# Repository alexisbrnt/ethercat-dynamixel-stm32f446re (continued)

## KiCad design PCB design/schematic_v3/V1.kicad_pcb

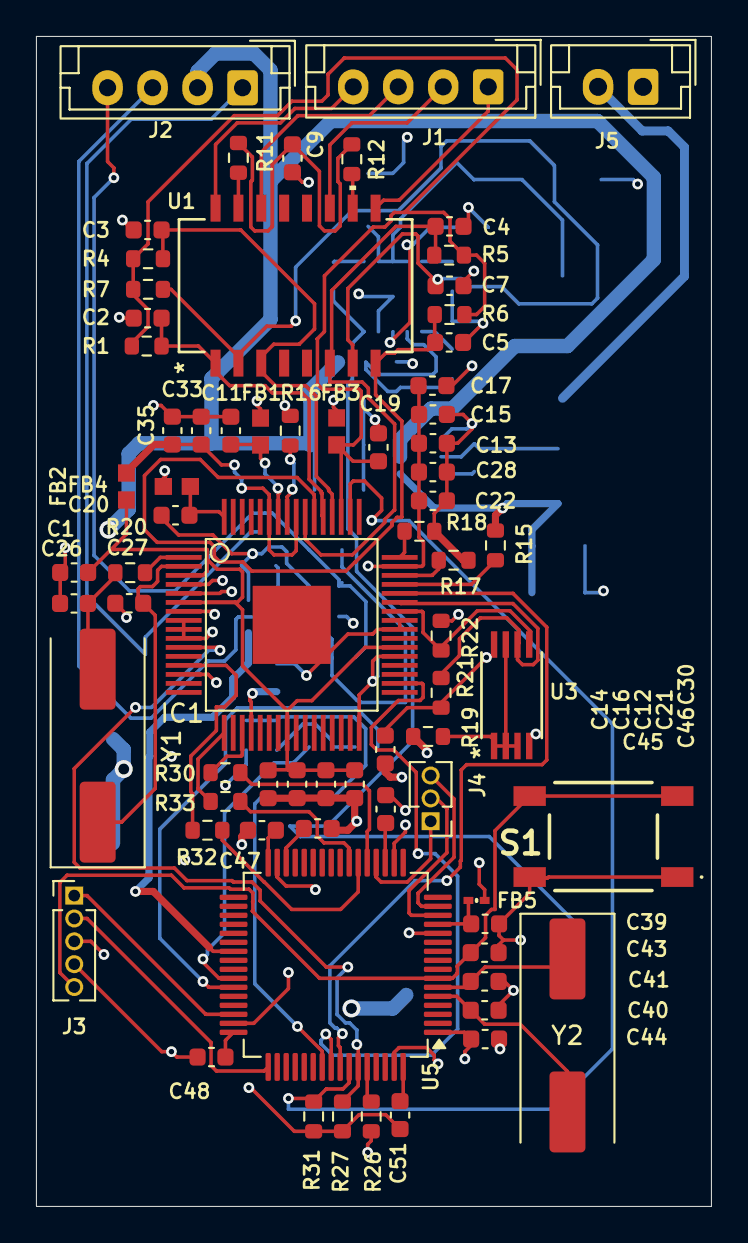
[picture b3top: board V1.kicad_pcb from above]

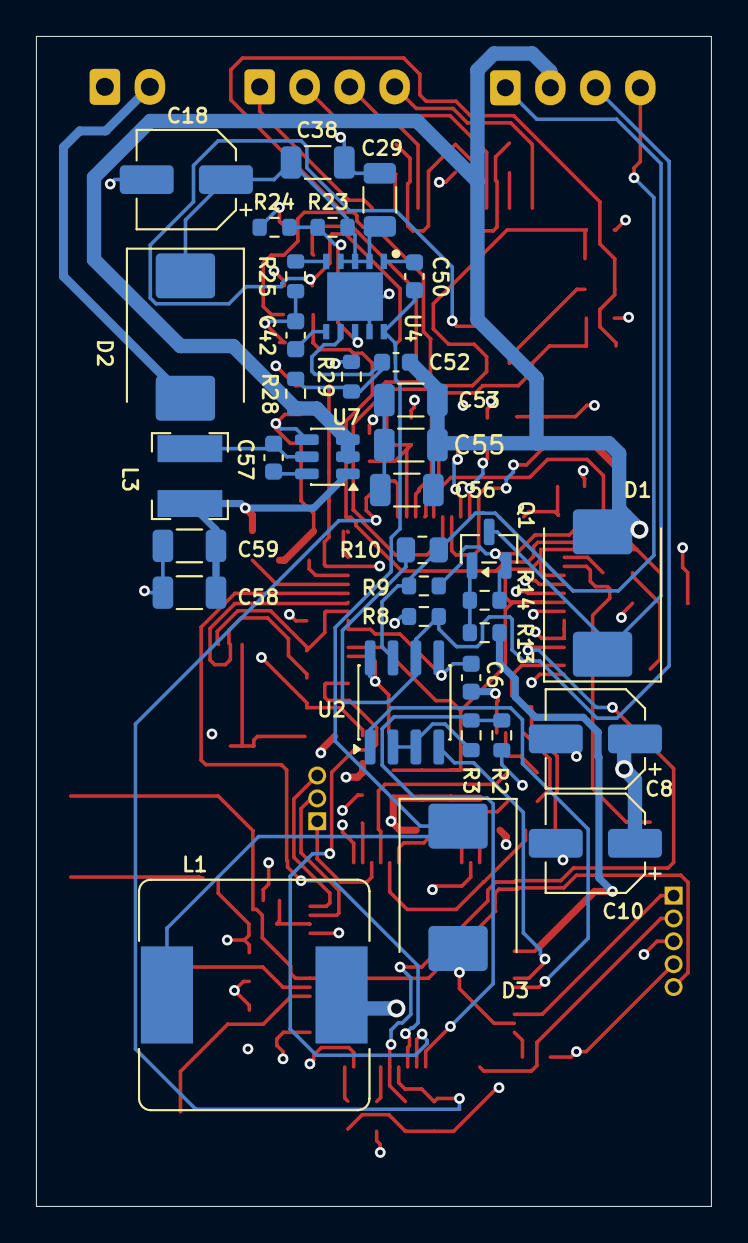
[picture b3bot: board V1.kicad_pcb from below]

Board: 4 copper layers, 37.5 x 65.0 mm, 108 parts (36 on the bottom side), 74 nets.

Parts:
C1, C6, C11, C13, C15, C16, C17, C21, C22, C28, C30, C33, C35: 0.1u; C_0603_1608Metric
C2, C3, C4, C5: 10p; C_0603_1608Metric
C7: 0.022u; C_0603_1608Metric
C8, C10, C18: 47u; CP_Elec_5x5.4
C9: 1n; C_0603_1608Metric
C12, C19, C20, C44: 1u; C_0603_1608Metric
C14: 470p; C_0603_1608Metric
C26, C27: 18p; C_0603_1608Metric
C29, C56: 10u; C_1206_3216Metric
C38: 100n; C_1206_3216Metric
C39, C42, C43, C46, C47, C48, C50, C51, C57: 100n; C_0603_1608Metric
C40, C41: 20p; C_0603_1608Metric
C45: 4.7u; C_0603_1608Metric
C52: 270p; C_0603_1608Metric
C53, C55: 27u; C_1206_3216Metric
C58, C59: 22u; C_1206_3216Metric
D1, D2, D3: B340; D_SMC
FB1, FB2, FB3, FB4: BLM18EG221SN1D; IND_BLM18_0603_MUR
FB5: MMZ0603A471ET000
IC1: TQFP64; LAN9252
J1: Conn_01x04_Pin; JST_EH_B4B-EH-A_1x04_P2.50mm_Vertical
J2: connection_moteur; JST_EH_B4B-EH-A_1x04_P2.50mm_Vertical
J3: Conn_01x05_Pin; PinHeader_1x05_P1.27mm_Vertical
J4: Conn_01x03_Pin; PinHeader_1x03_P1.27mm_Vertical
J5: Conn_01x02_Pin; JST_EH_B2B-EH-A_1x02_P2.50mm_Vertical
L1: 18u; L_Bourns_SRR1260
L3: 6.8u; L_Bourns-SRN4018
Q1: AO3400A; SOT-23
R1, R4, R5, R6: 49.9; R_0603_1608Metric
R2: 47k; R_0603_1608Metric
R3, R14, R15, R17, R18, R24, R26, R27, R29, R31: 10k; R_0603_1608Metric
R7, R20: 0; R_0603_1608Metric
R8, R9, R25: 20k; R_0603_1608Metric
R10: 120; R_0805_2012Metric
R11, R12: 75; R_0603_1608Metric
R13: 220; R_0603_1608Metric
R16: 12.1k; R_0603_1608Metric
R19: 4.7k; R_0603_1608Metric
R21, R22: 2k; R_0603_1608Metric
R23: 68k; R_0603_1608Metric
R28: 150k; R_0603_1608Metric
R30, R32, R33: 33; R_0603_1608Metric
S1: TS40-66-43-BK-260-SMT-TR
U1: HX1188NL
U2: SP3485CN; SOIC-8_3.9x4.9mm_P1.27mm
U3: 24FC512-I/ST; 24FC512_I_ST
U4: LMR14030SQDPRTQ1
U5: STM32F446RETx; LQFP-64_10x10mm_P0.5mm
U7: AP63203WU; TSOT-23-6
Y1: 25MHz; Crystal_SMD_HC49-SD
Y2: 8MHz; Crystal_SMD_HC49-SD

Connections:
+3.3V: C6.1, C13.1, C15.1, C17.1, C22.1, C28.1, C30.2, C44.2, C46.1, C47.1, C48.1, C51.1, C58.1, C59.1, FB1.1, FB3.2, FB4.2, FB5.1, IC1.5 (VDD33), IC1.7 (REG_EN), IC1.14 (VDDIO0), IC1.20 (VDDIO1), IC1.32 (VDDIO2), IC1.37 (VDDIO3), IC1.47 (VDDIO4), J3.4, L3.2, R8.2, R15.1, R21.2, R22.2, R27.1, R31.1, U2.8 (VCC), U3.8 (VCC), U5.1 (VBAT), U7.1 (FB)
+12V: C8.1, C10.1, C52.1, C53.1, C55.1, C56.1, D1.2 (A), J2.2, L1.2, R28.1, U7.2 (EN), U7.3 (IN)
+36V: D2.2 (A), J5.2
/ALIM_MOTOR: R13.2, U5.39 (PC8)
/AVDD: C39.1, FB5.2, U5.13 (VDDA)
/DI: U2.4 (DI), U5.42 (PA9)
/I2C_SCL: IC1.43 (EESCL/TCK), R21.1, U3.6 (SCL)
/I2C_SDL: IC1.42 (EESDA/TMS), R22.1, U3.5 (SDA)
/IRQ: IC1.44 (IRQ), U5.57 (PB5)
/MISO: IC1.13 (D1/AD1/EOF/SO/SIO1), R32.1
/MOSI: IC1.17 (D0/AD0/WD_STATE/SI/SIO0), R33.1
/NRST: C43.2, J3.5, S1.3 (NO_1), S1.4 (NO_2), U5.7 (NRST)
/OSCI: IC1.1 (OSCI), R20.1
/OSCO: C27.2, IC1.2 (OSCO), Y1.1
/RO: U2.1 (RO), U5.43 (PA10)
/RS485_MODE: R2.2, R3.2, U5.55 (PB3)
/RST#: IC1.11 (RST#), R27.2, U5.59 (PB7)
/RXA_N: C5.1, IC1.54 (RXNA), R6.2, U1.8 (RD-)
/RXA_P: C4.1, IC1.55 (RXPA), R5.2, U1.6 (RD+)
/SCK: IC1.19 (D9/AD9/LATCH_IN/SCK), R30.1
/SCS#: IC1.50 (D5/AD5/OUTVALID/SCS#), R31.2, U5.58 (PB6)
/SWCLK: J3.2, U5.49 (PA14)
/SWDIO: J3.1, U5.46 (PA13)
/SYNC0: IC1.34 (SYNC0/LATCH0), U5.56 (PB4)
/TXA_N: C3.1, IC1.52 (TXNA), R4.2, U1.3 (TD-)
/TXA_P: C2.1, IC1.53 (TXPA), R1.2, U1.1 (TD+)
/VDD12TX1: C33.1, C35.1, FB2.2, IC1.56 (VDD12TX1), IC1.59 (VDD12TX2)
/VDD33TXRX1: C19.1, FB3.1, IC1.51 (VDD33TXRX1), R1.1, R4.1, R5.1, R6.1, R7.1
/VDD33TXRX2: C20.1, FB4.1, IC1.64 (VDD33TXRX2)
/VDDCR: C1.2, C12.1, C14.1, C16.1, C21.1, FB2.1, IC1.3 (OSCVDD12), IC1.6 (VDDCR0), IC1.24 (VDDCR1), IC1.38 (VDDCR2)
GND: C1.1, C2.2, C3.2, C4.2, C5.2, C6.2, C7.2, C8.2, C9.2, C10.2, C11.1, C12.2, C13.2, C14.2, C15.2, C16.2, C17.2, C18.2, C19.2, C20.2, C21.2, C22.2, C26.1, C27.1, C28.2, C29.2, C30.1, C33.2, C35.2, C38.2, C39.2, C40.1, C41.1, C42.2, C43.1, C44.1, C45.2, C53.2, C55.2, C56.2, C58.2, C59.2, D3.2 (A), IC1.4 (OSCVSS), IC1.8 (FXLOSEN), IC1.9 (FXSDA/FXLOSA/FXSDENA), IC1.10 (FXSDB/FXLOSB/FXSDENB), IC1.40 (D8/AD8/DIGIO2/GPI2/GPO2/MII_MDIO), IC1.41 (TESTMODE), IC1.65 (VSS), J3.3, J5.1, Q1.2 (S), R2.1, R9.1, R14.1, R16.1, R17.1, R18.1, R19.2, R24.2, R25.2, R26.2, R29.2, S1.1 (COM_1), S1.2 (COM_2), U2.5 (GND), U3.4 (VSS), U4.9 (GND), U4.11 (PAD), U5.12 (VSSA), U5.18 (VSS), U5.31 (VSS), U5.47 (VSS), U5.63 (VSS), U7.4 (GND)
unnamed: C9.1, R11.1, R12.1
unnamed: C26.2, R20.2, Y1.2
unnamed: C46.2, U5.19 (VDD)
unnamed: C47.2, U5.32 (VDD)
unnamed: C48.2, U5.48 (VDD)
unnamed: C51.2, U5.64 (VDD)
unnamed: D1.1 (K), J2.1, Q1.3 (D)
unnamed: C18.1, C29.1, C38.1, D2.1 (K), R23.1, U4.2 (VIN), U4.3 (VIN), U4.4 (EN)
unnamed: C50.2, D3.1 (K), L1.1, U4.10 (SW)
unnamed: IC1.48 (LINKACTLED0/TDO/CHIP_MODE0), R18.2
unnamed: IC1.46 (LINKACTLED1/TDI/CHIP_MODE1), R17.2
unnamed: IC1.57 (RBIAS), R16.2
unnamed: IC1.45 (RUNLED/E2PSIZE), R15.2
unnamed: C11.2, FB1.2, IC1.58 (VDD33BIAS)
unnamed: J1.1, U1.9 (RX-)
unnamed: J1.2, U1.11 (RX+)
unnamed: J1.3, U1.14 (TX-)
unnamed: J1.4, U1.16 (TX+)
unnamed: J2.3, R8.1, R10.2, U2.6 (A)
unnamed: J2.4, R9.2, R10.1, U2.7 (B)
unnamed: J4.1, U5.20 (PA4)
unnamed: J4.2, U5.14 (PA0)
unnamed: J4.3, U5.15 (PA1)
unnamed: Q1.1 (G), R13.1, R14.2
unnamed: R11.2, U1.15 (CMT)
unnamed: R12.2, U1.10 (CMT)
unnamed: C7.1, R7.2, U1.2 (TCT), U1.7 (RCT)
unnamed: R3.1, U2.2 (~RE), U2.3 (DE)
unnamed: R19.1, U3.1 (A0), U3.2 (A1), U3.3 (A2), U3.7 (WP)
unnamed: C50.1, U4.1 (BOOT)
unnamed: C52.2, R28.2, R29.1, U4.7 (FB)
unnamed: R23.2, R24.1, U4.8 (PGOOD)
unnamed: R25.1, U4.5 (RT_SYNC)
unnamed: C42.1, U4.6 (SS)
unnamed: R26.1, U5.60 (BOOT0)
unnamed: R30.2, U5.21 (PA5)
unnamed: R32.2, U5.22 (PA6)
unnamed: R33.2, U5.23 (PA7)
unnamed: C40.2, U5.5 (PH0), Y2.2
unnamed: C41.2, U5.6 (PH1), Y2.1
unnamed: C45.1, U5.30 (VCAP_1)
unnamed: C57.2, U7.6 (BST)
unnamed: C57.1, L3.1, U7.5 (SW)

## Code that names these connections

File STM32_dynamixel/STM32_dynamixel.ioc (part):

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Mcu.Name=STM32F446R(C-E)Tx
Mcu.Package=LQFP64
Mcu.UserName=STM32F446RETx
PA0-WKUP.GPIOParameters=GPIO_PuPd
PA0-WKUP.GPIO_PuPd=GPIO_PULLUP
PA0-WKUP.Signal=GPIO_Input
PA1.GPIOParameters=GPIO_PuPd
PA1.GPIO_PuPd=GPIO_PULLUP
PA1.Signal=GPIO_Input
PA10.Mode=Asynchronous
PA10.Signal=USART1_RX
PA13.Mode=Serial_Wire
PA13.Signal=SYS_JTMS-SWDIO
PA14.Mode=Serial_Wire
PA14.Signal=SYS_JTCK-SWCLK
PA2.Mode=Asynchronous
PA2.Signal=USART2_TX
PA3.Mode=Asynchronous
PA3.Signal=USART2_RX
PA4.Signal=GPIO_Input
PA5.Mode=Full_Duplex_Master
PA5.Signal=SPI1_SCK
PA6.Mode=Full_Duplex_Master
PA6.Signal=SPI1_MISO
PA7.Mode=Full_Duplex_Master
PA7.Signal=SPI1_MOSI
PA9.Mode=Asynchronous
PA9.Signal=USART1_TX
PB10.Signal=GPIO_Output
PB3.Signal=GPIO_Output
PB4.Signal=GPXTI4
PB5.Signal=GPXTI5
PB6.Signal=GPIO_Output
PB7.Signal=GPIO_Output
board=custom

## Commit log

2026-04-16 MAJ README
2026-04-16 cleaning code
2026-04-16 mise a jour partie eepromtool
2026-04-22 Developpement des Input/Output
2026-04-22 ajout des conditions limites
2026-04-22 Refactor README.md for improved clarity and formatting
2026-04-23 update of the control current
2026-04-23 Remove badge images from README
    Removed badge images from the README file.
2026-04-24 ajout des sensors
2026-04-28 ajout de la détection de limite
2026-04-28 ajout de la fonction reboot
2026-04-29 reboot après emergency state
2026-05-06 implementation of some requirements
2026-05-11 update week 20
2026-05-12 State machine implemented
2026-05-12 update 12_05
2026-05-21 update iplink value
2026-05-27 update pcb design
2026-06-03 03/06
2026-06-16 pcb updated
2026-06-17 1KHz ecat communication frequency done
2026-06-17 1KHz
2026-06-25 PCB ordered
